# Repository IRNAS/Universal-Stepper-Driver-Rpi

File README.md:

# Universal Stepper Driver RPi

Here you can find documentation for Universal stepper driver in shape of Raspberry Pi Hat. It supports all signals for Bipolar stepper motors thrue RPi header and have Unipolar stepper connectors and drivers. This driver is GRBL comatibile.

#### Features
- switching power supplay
- USB connector
- current mesurment
- unipolar stepper motor drivers on board
- RPi connector
- encoder connectors
- endswitch connector
- universal serial connector
- 2x LED
- 1x push button

#### Hardware
Schematics and PCB are designed with open source EDA tool KiCad, all nesesery design files are in this repository.

#### Software
Firmware and all the nessery documentation for Universal Stepper Driver RPi can be found in this [repository](https://github.com/IRNAS/grbl_stm32).

This is currently in testing phase.

#### Known Isues
- Universal serial connector footprint is not good, need to be changed

---

#### License

All our projects are as usefully open-source as possible.

Hardware including documentation is licensed under [CERN OHL v.1.2. license](http://www.ohwr.org/licenses/cern-ohl/v1.2)

Firmware and software originating from the project is licensed under [GNU GENERAL PUBLIC LICENSE v3](http://www.gnu.org/licenses/gpl-3.0.en.html).

Open data generated by our projects is licensed under [CC0](https://creativecommons.org/publicdomain/zero/1.0/legalcode).

All our websites and additional documentation are licensed under [Creative Commons Attribution-ShareAlike 4 .0 Unported License] (https://creativecommons.org/licenses/by-sa/4.0/legalcode).

What this means is that you can use hardware, firmware, software and documentation without paying a royalty and knowing that you'll be able to use your version forever. You are also free to make changes but if you share these changes then you have to do so on the same conditions that you enjoy.

Koruza, GoodEnoughCNC and IRNAS are all names and marks of Institut IRNAS Rače. 
You may use these names and terms only to attribute the appropriate entity as required by the Open Licences referred to above. You may not use them in any other way and in particular you may not use them to imply endorsement or authorization of any hardware that you design, make or sell.

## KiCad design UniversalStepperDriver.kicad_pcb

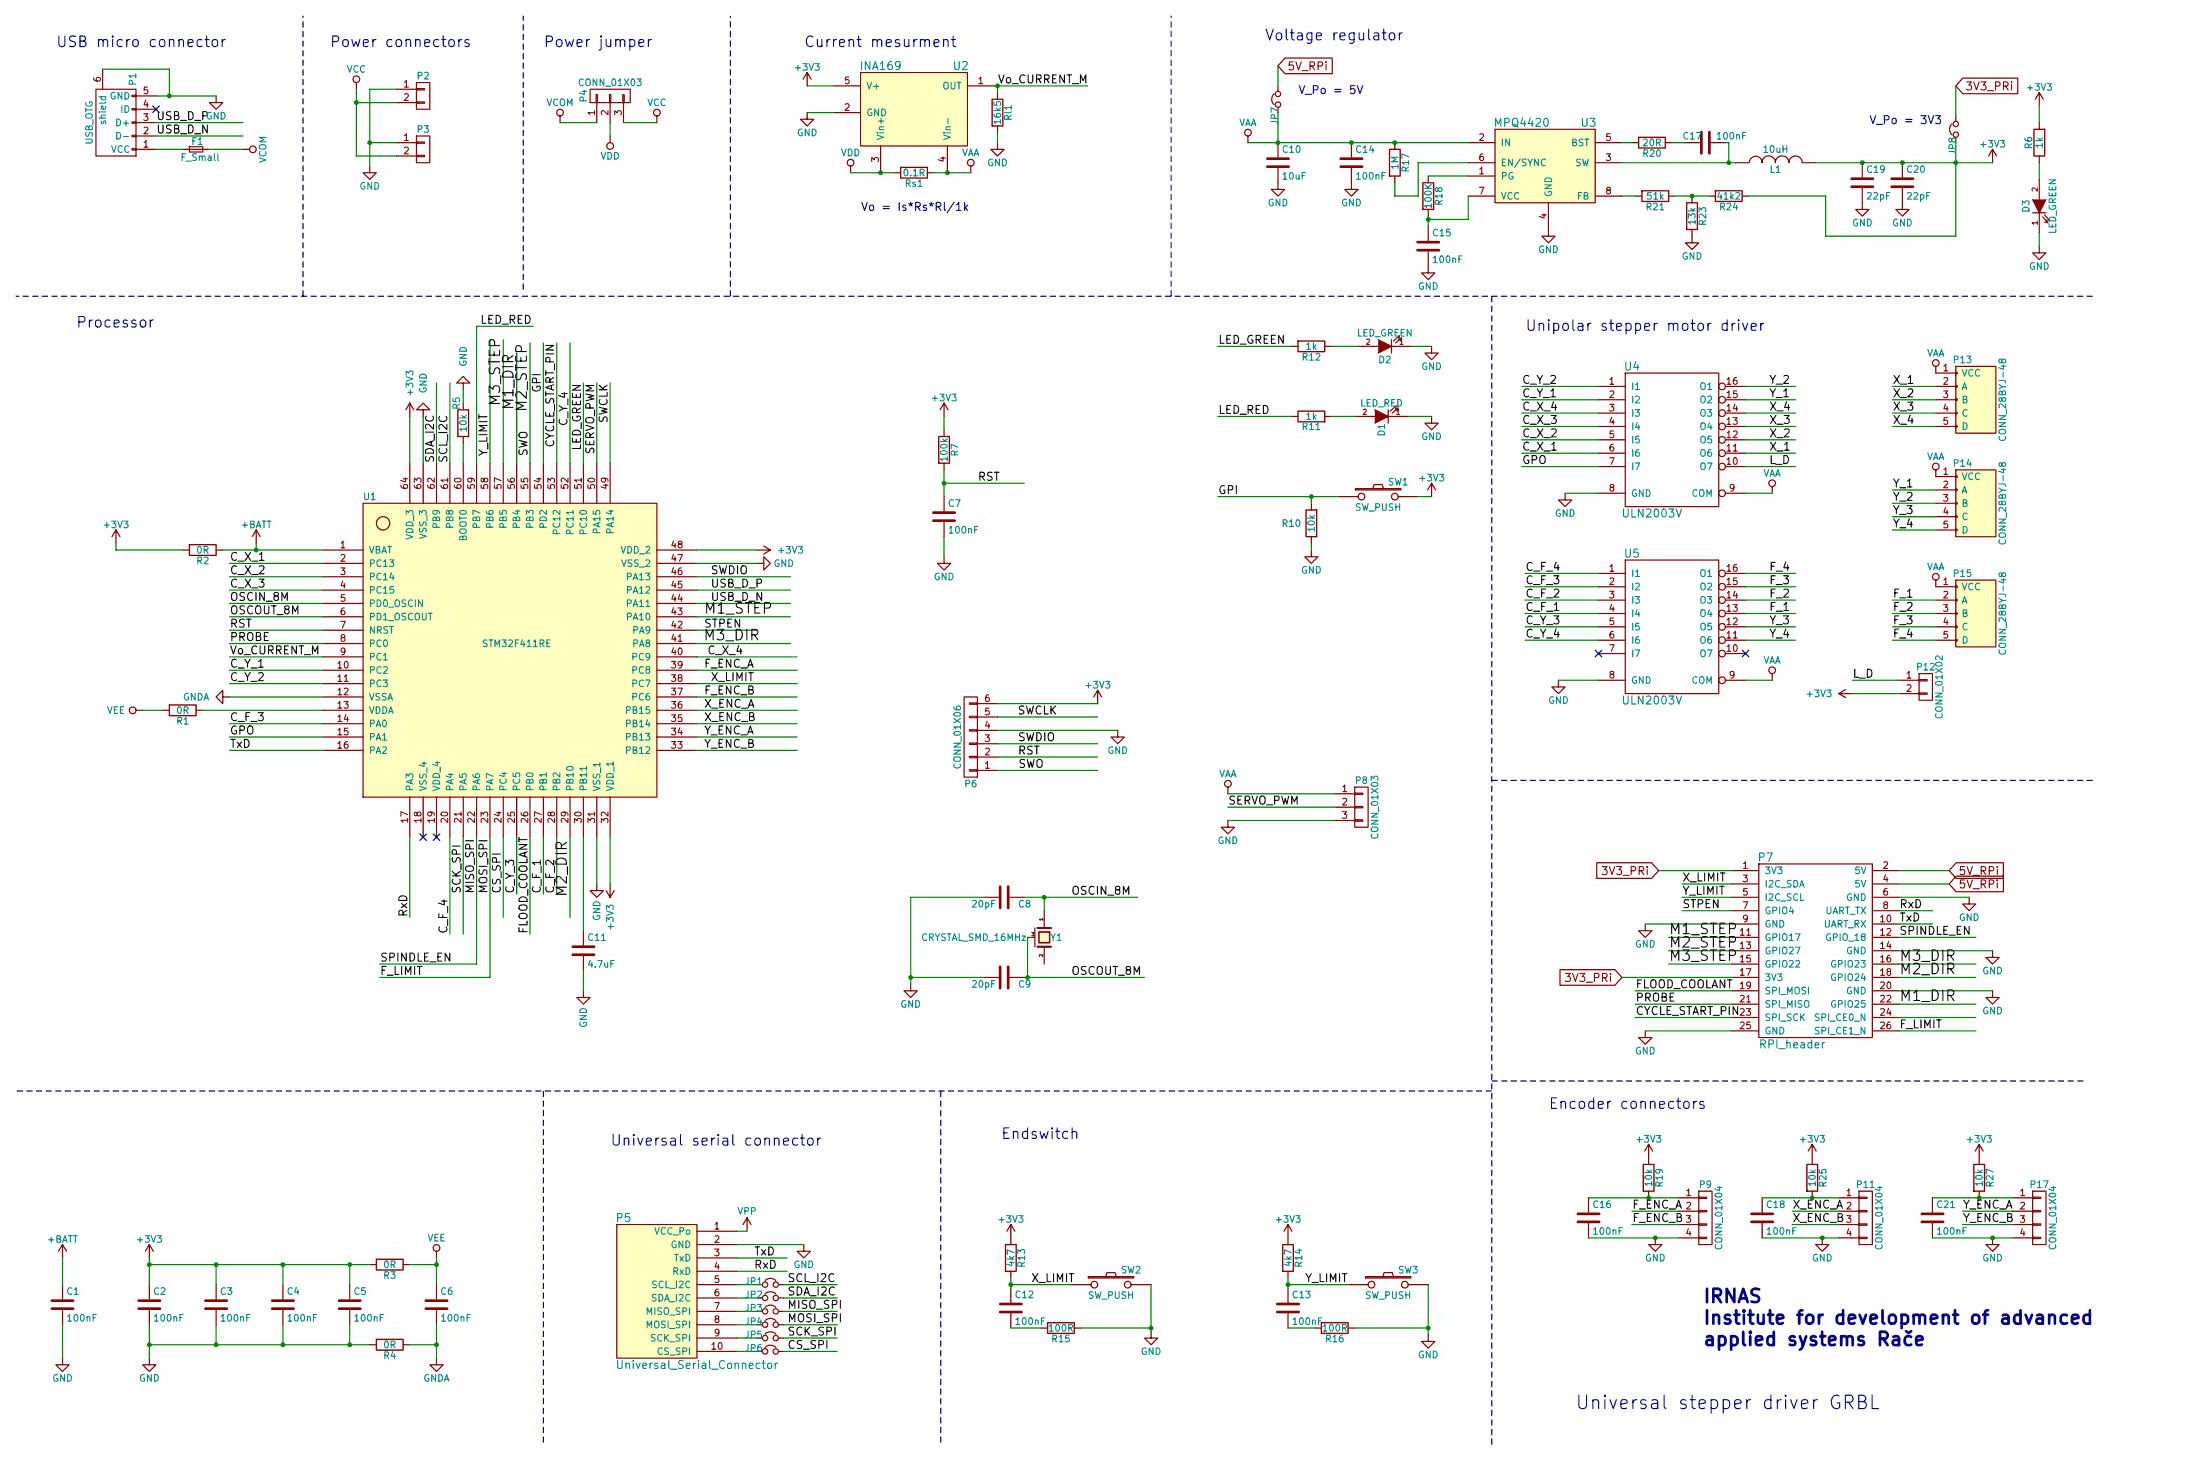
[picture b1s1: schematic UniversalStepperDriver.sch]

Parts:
C1, C2, C3, C4, C5, C6, C7, C12, C13, C14, C15, C16, C17, C18, C21: 100nF; C_0603
C8, C9: 20pF; C_0603
C10: 10uF; C_0603
C11: 4.7uF; C_0805
C19, C20: 22pF; C_0603
D1: LED_RED; LED_0603
D2, D3: LED_GREEN; LED_0603
F1: F_Small; Fuse_SMD1206_Reflow
JP1, JP2, JP3, JP4, JP5, JP6, JP7, JP8: Jumper_NC_Small; bridgeJumper
L1: 10uH; Inductor SMD XAL50
P1: USB_OTG; USB_Micro-B_10103594-0001LF
P2, P3: CONN_01X02; terminal_block_dc_jack_5mm_wide
P4, P8: CONN_01X03; Pin_Header_Straight_1x03
P5: Universal_Serial_Connector; micromatch
P6: CONN_01X06; Pin_Header_Straight_1x06
P7: RPI_header; Pin_Header_Straight_2x13
P9, P11, P17: CONN_01X04; Pin_Header_Straight_1x04
P12: CONN_01X02; Pin_Header_Straight_1x02
P13, P14, P15: CONN_28BYJ-48; 28BYJ-48
R1, R2, R3, R4: 0R; R_0603
R5, R10, R19, R25, R27: 10k; R_0603
R6, R11, R12: 1k; R_0603
R7: 100k; R_0603
R13, R14: 4k7; R_0603
R15, R16: 100R; R_0603
R17: 1M; R_0603
R18: 100K; R_0603
R20: 20R; R_0603
R21: 51k; R_0603
R23: 13k; R_0603
R24: 41k2; R_0603
Rl1: 16k5; R_0603
Rs1: 0.1R; R_1812
SW1: SW_PUSH; KSEK43J_LFS_TACTILE_SWITCH
SW2, SW3: SW_PUSH; SW_Tactile_SPST_Angled
U1: STM32F411RE; QFP_64
U2: INA169; SOT-23-5
U3: MPQ4420; TSOT32-8
U4, U5: ULN2003V; R-PDSO-G16
Y1: CRYSTAL_SMD_16MHz; SPK5032

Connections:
3V3_PRi: JP8.2, P7.1 (3V3), P7.17 (3V3)
5V_RPi: JP7.2, P7.2 (5V), P7.4 (5V)
+3V3: C2.1, C3.1, C4.1, C5.1, C19.1, C20.1, JP8.1, L1.2, P6.6, P12.2, R2.2, R3.2, R6.2, R7.1, R13.1, R14.1, R19.1, R24.1, R25.1, R27.1, SW1.2, U1.32 (VDD_1), U1.48 (VDD_2), U1.64 (VDD_3), U2.5 (V+)
+BATT: C1.1, R2.1, U1.1 (VBAT)
/CS_SPI: JP6.2, U1.24 (PC4)
/CYCLE_START_PIN: P7.23 (SPI_SCK), U1.53 (PC12)
/C_F_1: U1.27 (PB1), U5.4 (I4)
/C_F_2: U1.28 (PB2), U5.3 (I3)
/C_F_3: U1.14 (PA0), U5.2 (I2)
/C_F_4: U1.20 (PA4), U5.1 (I1)
/C_X_1: U1.2 (PC13), U4.6 (I6)
/C_X_2: U1.3 (PC14), U4.5 (I5)
/C_X_3: U1.4 (PC15), U4.4 (I4)
/C_X_4: U1.40 (PC9), U4.3 (I3)
/C_Y_1: U1.10 (PC2), U4.2 (I2)
/C_Y_2: U1.11 (PC3), U4.1 (I1)
/C_Y_3: U1.25 (PC5), U5.5 (I5)
/C_Y_4: U1.52 (PC11), U5.6 (I6)
/FLOOD_COOLANT: P7.19 (SPI_MOSI), U1.26 (PB0)
/F_1: P15.2 (A), U5.13 (O4)
/F_2: P15.3 (B), U5.14 (O3)
/F_3: P15.4 (C), U5.15 (O2)
/F_4: P15.5 (D), U5.16 (O1)
/F_ENC_A: P9.2, U1.39 (PC8)
/F_ENC_B: P9.3, U1.37 (PC6)
/F_LIMIT: JP4.2, P7.26 (SPI_CE1_N), U1.23 (PA7)
/GPI: R10.2, SW1.1, U1.54 (PD2)
/GPO: U1.15 (PA1), U4.7 (I7)
/LED_GREEN: R12.2, U1.51 (PC10)
/LED_RED: R11.1, U1.59 (PB7)
/L_D: P12.1, U4.10 (O7)
/M1_DIR: P7.22 (GPIO25), U1.56 (PB4)
/M1_STEP: P7.11 (GPIO17), U1.43 (PA10)
/M2_DIR: P7.18 (GPIO24), U1.29 (PB10)
/M2_STEP: P6.1, P7.13 (GPIO27), U1.55 (PB3)
/M3_DIR: P7.16 (GPIO23), U1.41 (PA8)
/M3_STEP: P7.15 (GPIO22), U1.57 (PB5)
/MISO_SPI: JP3.2, P7.12 (GPIO_18), U1.22 (PA6)
/OSCIN_8M: C8.1, U1.5 (PD0_OSCIN), Y1.1
/OSCOUT_8M: C9.1, U1.6 (PD1_OSCOUT), Y1.3 (case)
/PROBE: P7.21 (SPI_MISO), U1.8 (PC0)
/RST: C7.1, P6.2, R7.2, U1.7 (NRST)
/RxD: P5.4 (RxD), P7.8 (UART_TX), U1.17 (PA3)
/SCK_SPI: JP5.2, U1.21 (PA5)
/SCL_I2C: JP1.2, U1.61 (PB8)
/SDA_I2C: JP2.2, U1.62 (PB9)
/SERVO_PWM: P8.2, U1.50 (PA15)
/STPEN: P7.7 (GPIO4), U1.42 (PA9)
/SWCLK: P6.5, U1.49 (PA14)
/SWDIO: P6.3, U1.46 (PA13)
/TxD: P5.3 (TxD), P7.10 (UART_RX), U1.16 (PA2)
/USB_D_N: P1.2 (D-), U1.44 (PA11)
/USB_D_P: P1.3 (D+), U1.45 (PA12)
/Vo_CURRENT_M: Rl1.1, U1.9 (PC1), U2.1 (OUT)
/X_1: P13.2 (A), U4.11 (O6)
/X_2: P13.3 (B), U4.12 (O5)
/X_3: P13.4 (C), U4.13 (O4)
/X_4: P13.5 (D), U4.14 (O3)
/X_ENC_A: P11.2, U1.36 (PB15)
/X_ENC_B: P11.3, U1.35 (PB14)
/X_LIMIT: C12.1, P7.3 (I2C_SDA), R13.2, SW2.1, U1.38 (PC7)
/Y_1: P14.2 (A), U4.15 (O2)
/Y_2: P14.3 (B), U4.16 (O1)
/Y_3: P14.4 (C), U5.12 (O5)
/Y_4: P14.5 (D), U5.11 (O6)
/Y_ENC_A: P17.2, U1.34 (PB13)
/Y_ENC_B: P17.3, U1.33 (PB12)
/Y_LIMIT: C13.1, P7.5 (I2C_SCL), R14.2, SW3.1, U1.58 (PB6)
GND: C1.2, C2.2, C3.2, C4.2, C5.2, C7.2, C8.2, C9.2, C10.2, C11.2, C14.2, C15.2, C16.2, C18.2, C19.2, C20.2, C21.2, D1.1 (K), D2.1 (K), D3.1 (K), P1.5 (GND), P1.6 (shield), P2.1, P3.1, P5.2 (GND), P6.4, P7.6 (GND), P7.9 (GND), P7.14 (GND), P7.20 (GND), P7.25 (GND), P8.3, P9.4, P11.4, P17.4, R4.2, R5.1, R10.1, R15.1, R16.1, R23.2, Rl1.2, SW2.2, SW3.2, U1.31 (VSS_1), U1.47 (VSS_2), U1.63 (VSS_3), U2.2 (GND), U3.4 (GND), U4.8 (GND), U5.8 (GND)
GNDA: C6.2, R4.1, U1.12 (VSSA)
unnamed: C11.1, U1.30 (PB11)
unnamed: C12.2, R15.2
unnamed: C13.2, R16.2
unnamed: C15.1, R18.2, U3.7 (VCC)
unnamed: C16.1, P9.1, R19.2
unnamed: C17.1, L1.1, U3.3 (SW)
unnamed: C17.2, R20.1
unnamed: C18.1, P11.1, R25.2
unnamed: C21.1, P17.1, R27.2
unnamed: D1.2 (A), R11.2
unnamed: D2.2 (A), R12.1
unnamed: D3.2 (A), R6.1
unnamed: F1.1, P1.1 (VCC)
unnamed: JP1.1, P5.5 (SCL_I2C)
unnamed: JP2.1, P5.6 (SDA_I2C)
unnamed: JP3.1, P5.7 (MISO_SPI)
unnamed: JP4.1, P5.8 (MOSI_SPI)
unnamed: JP5.1, P5.9 (SCK_SPI)
unnamed: JP6.1, P5.10 (CS_SPI)
unnamed: R1.1, U1.13 (VDDA)
unnamed: R5.2, U1.60 (BOOT0)
unnamed: R17.2, U3.6 (EN/SYNC)
unnamed: R18.1, U3.1 (PG)
unnamed: R20.2, U3.5 (BST)
unnamed: R21.1, R23.1, R24.2
unnamed: R21.2, U3.8 (FB)
VAA: C10.1, C14.1, JP7.1, P8.1, P13.1 (VCC), P14.1 (VCC), P15.1 (VCC), R17.1, Rs1.1, U2.4 (Vin-), U3.2 (IN), U4.9 (COM), U5.9 (COM)
VCC: P2.2, P3.2, P4.3
VCOM: F1.2, P4.1
VDD: P4.2, Rs1.2, U2.3 (Vin+)
VEE: C6.1, R1.2, R3.1
VPP: P5.1 (VCC_Po)

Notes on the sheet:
Vo = Is*Rs*Rl/1k
V_Po = 5V
V_Po = 3V3
USB micro connector
Power connectors
Power jumper
Current mesurment
Voltage regulator
Unipolar stepper motor driver
Universal serial connector
Encoder connectors
Processor
IRNAS Institute for development of advanced applied systems Rače
Universal stepper driver GRBL
Endswitch

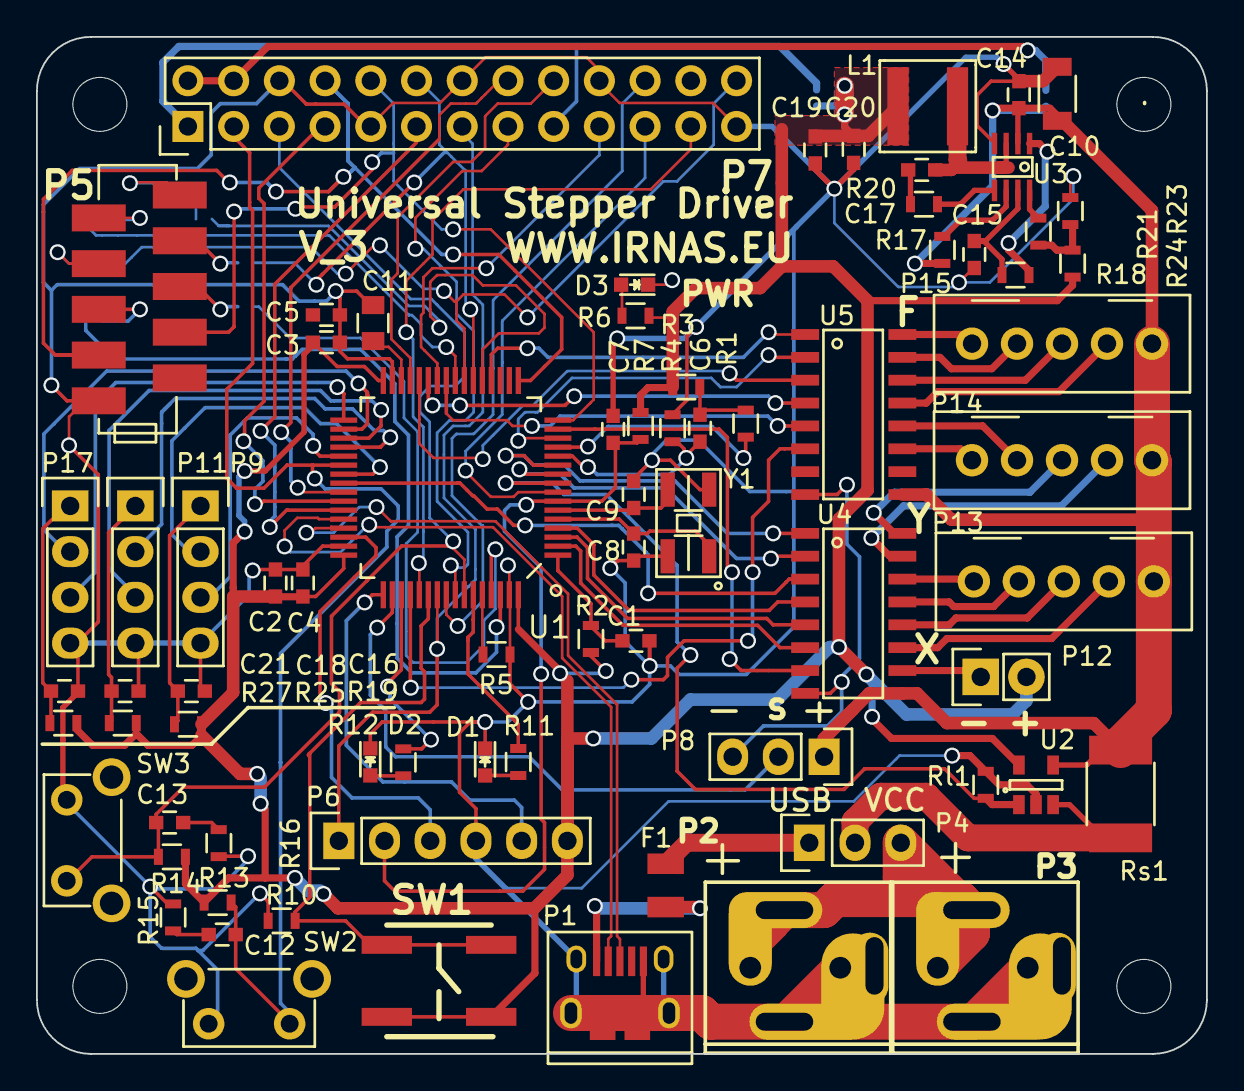
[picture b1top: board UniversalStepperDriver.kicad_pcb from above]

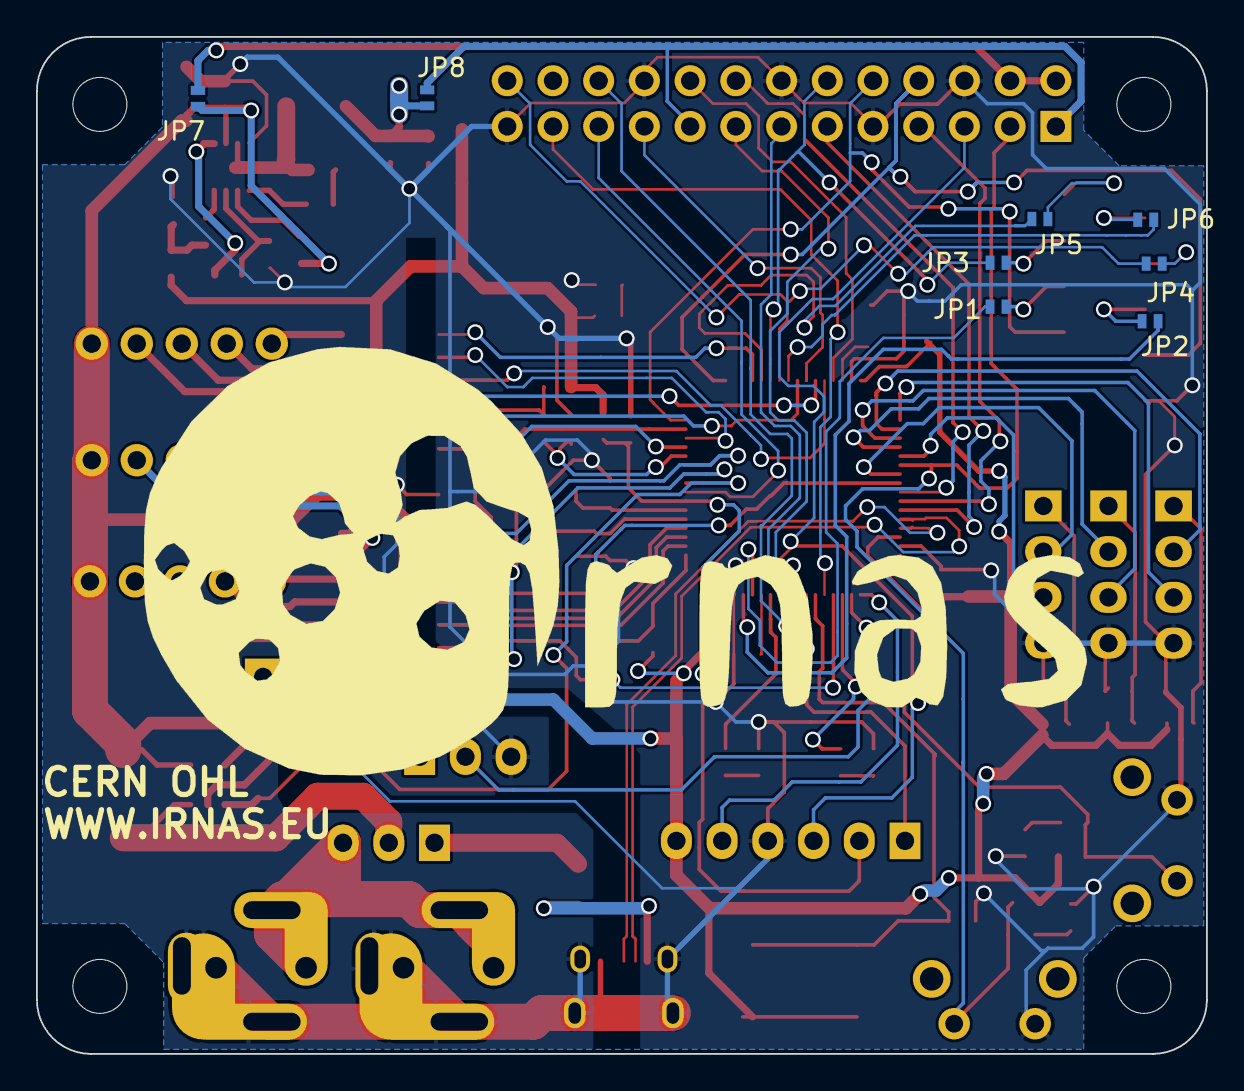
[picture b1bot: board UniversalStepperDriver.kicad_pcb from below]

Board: 2 copper layers, 65.0 x 56.5 mm, 83 parts (8 on the bottom side), 101 nets.

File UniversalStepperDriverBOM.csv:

"Id";"Designator";"Package";"Quantity";"Designation";"Supplier and ref";
1;"REF**,REF**,REF**,REF**";"MountingHole_3mm";4;"MountingHole_3mm";;;
2;"C1,C2,C3,C4,C5,C6,C7,C12,C13,C14,C15,C16,C17,C18,C21";"C_0603";15;"100nF";;;
3;"C8,C9";"C_0603";2;"20pF";;;
4;"C10";"C_0603";1;"10uF";;;
5;"C19,C20";"C_0603";2;"22pF";;;
6;"D1";"LED_0603";1;"LED_RED";;;
7;"D2";"LED_0603";1;"LED_GREEN";;;
8;"F1";"Fuse_SMD1206_Reflow";1;"F_Small";;;
9;"JP1,JP2,JP3,JP4,JP5,JP6,JP7,JP8";"bridgeJumper";8;"Jumper_NC_Small";;;
10;"L1";"Inductor SMD XAL50";1;"10uH";;;
11;"P1";"USB_Micro-B_10103594-0001LF";1;"USB_OTG";;;
12;"P2,P3";"terminal_block_dc_jack_5mm_wide";2;"CONN_01X02";;;
13;"P4,P8";"Pin_Header_Straight_1x03";2;"CONN_01X03";;;
14;"P5";"micromatch";1;"Universal_Serial_Connector";;;
15;"P6";"Pin_Header_Straight_1x06";1;"CONN_01X06";;;
16;"P7";"Pin_Header_Straight_2x13";1;"RPI_header";;;
17;"P9,P11,P17";"Pin_Header_Straight_1x04";3;"CONN_01X04";;;
18;"P12";"Pin_Header_Straight_1x02";1;"CONN_01X02";;;
19;"P13,P14,P15";"28BYJ-48";3;"CONN_28BYJ-48";;;
20;"R1,R2,R3,R4";"R_0603";4;"0R";;;
21;"R5,R10,R19,R25,R27";"R_0603";5;"10k";;;
22;"R7";"R_0603";1;"100k";;;
23;"R11,R12";"R_0603";2;"1k";;;
24;"R13,R14";"R_0603";2;"4k7";;;
25;"R15,R16";"R_0603";2;"100R";;;
26;"R17";"R_0603";1;"1M";;;
27;"R18";"R_0603";1;"100K";;;
28;"R20";"R_0603";1;"20R";;;
29;"R21";"R_0603";1;"51k";;;
30;"R23";"R_0603";1;"13k";;;
31;"R24";"R_0603";1;"41k2";;;
32;"Rl1";"R_0603";1;"16k5";;;
33;"Rs1";"R_1812";1;"0.1R";;;
34;"U1";"QFP_64";1;"STM32F411RE";;;
35;"U2";"SOT-23-5";1;"INA169";;;
36;"U3";"TSOT32-8";1;"MPQ4420";;;
37;"U4,U5";"R-PDSO-G16";2;"ULN2003V";;;
38;"Y1";"SPK5032";1;"CRYSTAL_SMD_16MHz";;;
39;"SW2,SW3";"SW_Tactile_SPST_Angled";2;"SW_PUSH";;;
40;"SW1";"KSEK43J_LFS_TACTILE_SWITCH";1;"SW_PUSH";;;
41;"G***";"LOGO_irnas1";1;"LOGO";;;

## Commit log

2016-04-18 all connected
2016-04-19 rev0.1 board done
2016-04-21 add gerber and BOM
2016-05-10 add picture for readme
2016-05-10 readme update
2016-07-18 P5 footprint fix
2016-07-18 P5 footprint Fixes #5
2016-07-18 PWR LED add Fixes #3
2016-07-18 add VCAP1 4.7u to PIN30(PB11) Fixes #2
2016-07-19 gerbers done for V3.1

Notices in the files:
UniversalStepperDriver.kicad_pcb:
License: CERN OHL V1.2
